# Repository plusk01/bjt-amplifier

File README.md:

# bjt-amplifier
BJT Amplifier design for BYU ECEn 340

</img>
</img>

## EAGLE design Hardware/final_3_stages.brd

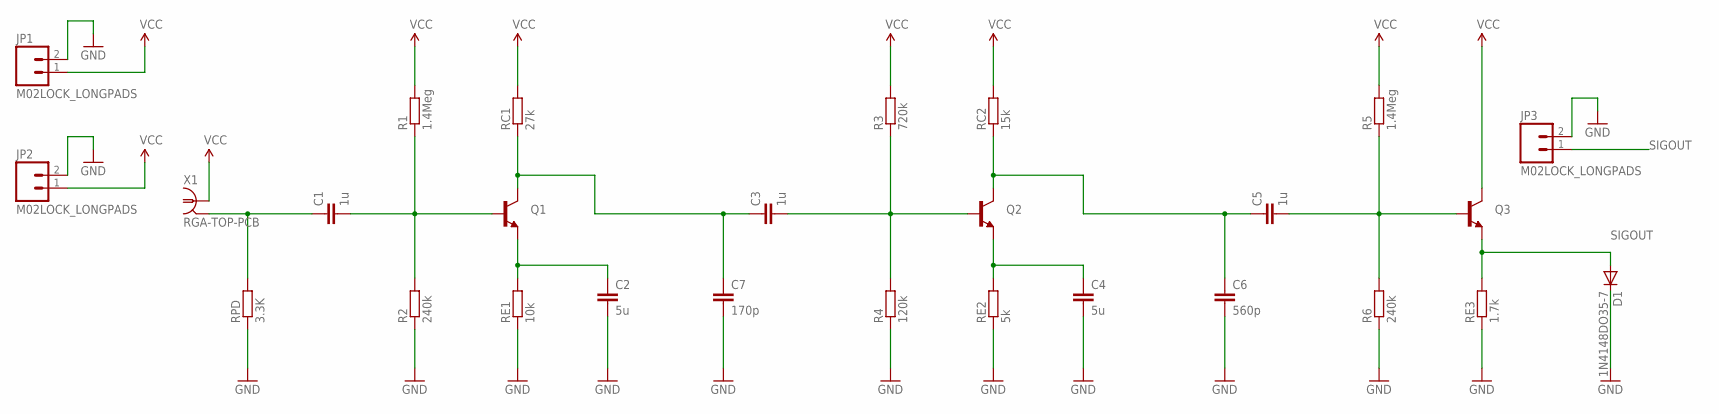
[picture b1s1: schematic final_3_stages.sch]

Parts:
C1, C3, C5: 1u; CAP-PTH-SMALL-KIT
C2, C4: 5u; CAP-PTH-SMALL-KIT
C6: 560p; CAP-PTH-SMALL-KIT
C7: 170p; CAP-PTH-SMALL-KIT
D1: 1N4148DO35-7; DO35-7
JP1, JP2, JP3: M02LOCK_LONGPADS; 1X02_LOCK_LONGPADS
Q1, Q2, Q3: TRANSISTOR_NPN2N3904; TO-92
R1, R5: 1.4Meg; 0207/10
R2, R6: 240k; 0207/10
R3: 720k; 0207/10
R4: 120k; 0207/10
RC1: 27k; 0207/10
RC2: 15k; 0207/10
RE1: 10k; 0207/10
RE2: 5k; 0207/10
RE3: 1.7k; 0207/10
RPD: 3.3K; 0207/10
X1: RGA-TOP-PCB; BNC-RGA

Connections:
GND: C2.2, C4.2, C6.2, C7.2, D1.C, JP1.2, JP2.2, JP3.2, R2.1, R4.1, R6.1, RE1.1, RE2.1, RE3.1, RPD.1
unnamed: C3.1, C7.1, Q1.3 (C), RC1.1
unnamed: C5.1, C6.1, Q2.3 (C), RC2.1
unnamed: C1.1, RPD.2, X1.2, X1.3 (2), X1.4 (2), X1.5 (2)
unnamed: C1.2, Q1.2 (B), R1.1, R2.2
unnamed: C3.2, Q2.2 (B), R3.1, R4.2
unnamed: C5.2, Q3.2 (B), R5.1, R6.2
unnamed: C2.1, Q1.1 (E), RE1.2
unnamed: C4.1, Q2.1 (E), RE2.2
SIGOUT: D1.A, JP3.1, Q3.1 (E), RE3.2
VCC: JP1.1, JP2.1, Q3.3 (C), R1.2, R3.2, R5.2, RC1.2, RC2.2, X1.1

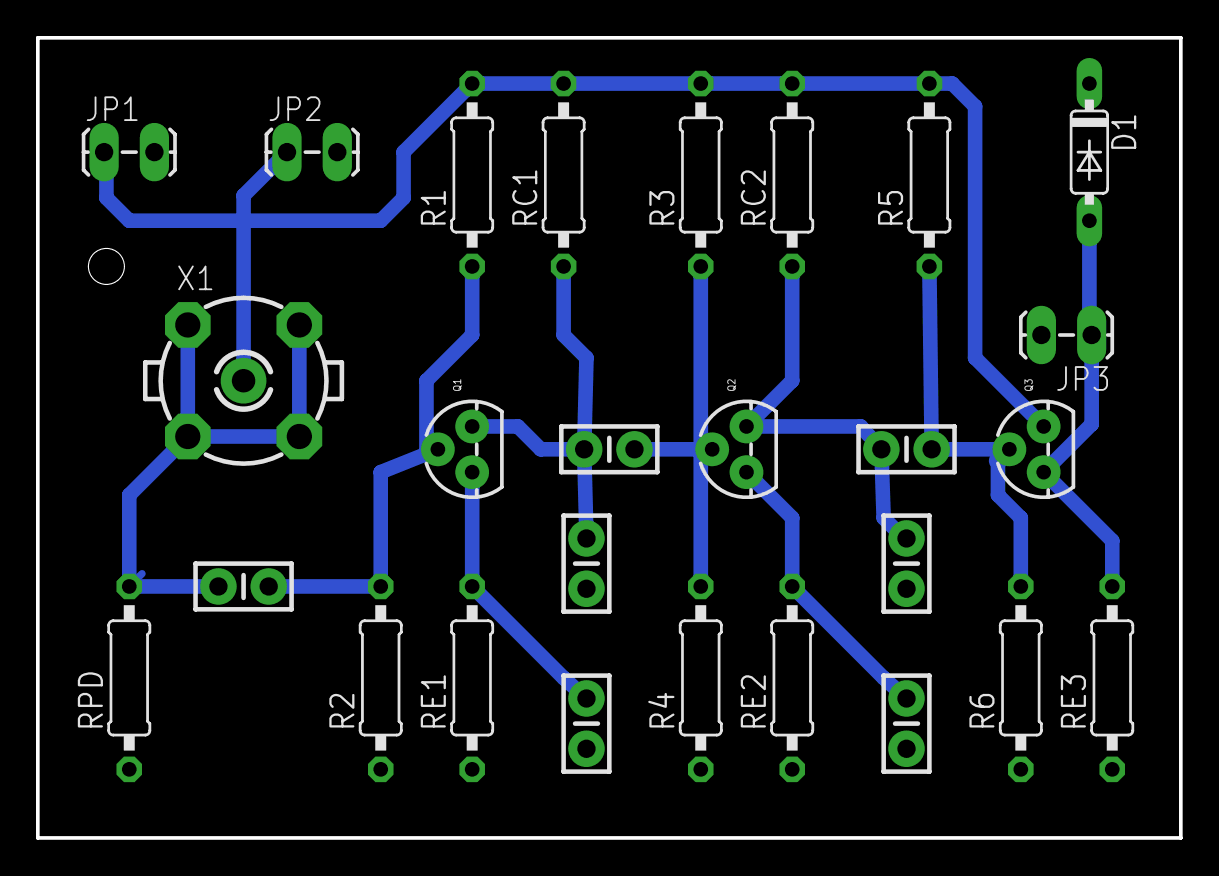
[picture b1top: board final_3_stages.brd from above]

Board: 2 copper layers, 63.5 x 44.5 mm, 27 parts (0 on the bottom side), 11 nets.

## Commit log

2015-08-04 added EAGLE files and pictures

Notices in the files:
parts and their libraries:
SparkFun-Connectors: Licensing: Creative Commons ShareAlike 4.0 International - https://creativecommons.org/licenses/by-sa/4.0
